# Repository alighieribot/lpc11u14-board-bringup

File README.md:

# Board Bring-Up e Validação de Protótipo Eletrônico Embarcado
## Plataforma de Instrumentação e Controle Baseada no MCU NXP LPC11U14F (ARM Cortex-M0)

)

Este repositório reúne a documentação técnica integral, os projetos de engenharia eletrônica (esquemático elétrico, layout de PCI de 2 camadas e modelos 3D desenvolvidos no KiCad 9) e o firmware embarcado modular em linguagem C (bare-metal) estruturado em **Máquina de Estados Finitos (FSM)** para validação física e *board bring-up* de uma placa com o microcontrolador **NXP LPC11U14F** (núcleo ARM Cortex-M0).

O projeto foi concebido e implementado no âmbito da disciplina **PBLE02 (Projeto Baseado em Laboratório de Engenharia / Projeto de Hardware e Firmware)** do **Instituto de Engenharia de Sistemas e Tecnologia da Informação (IESTI)** da **Universidade Federal de Itajubá (UNIFEI)**, sob a orientação do **Prof. Dr. Rodrigo Maximiano Antunes de Almeida**.

---

## Equipe do Projeto (Grupo 1)

| Integrante | Matrícula |
| :--- | :---: |
| **Leonardo Mendonça Costa** | `2024001025` |
| **Fabricio Augusto Antonio** | `2025000031` |
| **Pedro Henrique Oliveira Francisco** | `2022003245` |
| **Luis Gustavo Ribeiro Chacon** | `2025004890` |

**Agradecimentos Institucionais:**
À equipe técnica de laboratório do IESTI/UNIFEI, em especial aos técnicos em eletrônica **José Anderson Reis** e **Nedson Joaquim Maia**, pelo auxílio instrumental de bancada, suporte de montagem e retrabalho de protótipos; e ao **Prof. Dr. Rodrigo Maximiano Antunes de Almeida** pelas orientações e direcionamento técnico durante a validação experimental.

---

## Visão Geral da Placa de Circuito Impresso (PCB)

A placa física foi projetada respeitando dimensões compactas de $80 \times 80\text{ mm}^2$ em substrato de fibra de vidro FR-4 de duas camadas condutivas, espessura de 1,6 mm, acabamento superficial HASL com chumbo, máscara de solda verde e serigrafia branca, fabricada pela JLCPCB.

| Face Superior 3D (Revisão Final Corrigida) | Face Inferior 3D (Plano de Terra Sólido) |
| :---: | :---: |
|  |  |

| Comparativo Histórico: Face Superior 3D Original |
| :---: |
|  |

> **BOM Interativo (iBOM):** O repositório inclui a lista de materiais interativa gerada pelo plugin *Interactive HTML BOM*. Para navegar visualmente por cada componente, ilha e footprint na placa, abra em seu navegador o arquivo [`KiCad/Projeto_Final/bom/ibom.html`](KiCad/Projeto_Final/bom/ibom.html).

---

## Arquitetura de Hardware & Subcircuitos

O sistema é subdividido em 5 subsistemas funcionais integrados:

```mermaid
graph TD
    PS["1. Subcircuito de Alimentação<br/>Jack DC 7-12V -> LD1117 5.0V & 3.3V"] --> MCU["2. Processamento Central<br/>NXP LPC11U14F ARM Cortex-M0 @ 48MHz"]
    PS --> COMM["5. Comunicação Serial<br/>FTDI FT232RL USB-UART"]
    PS --> HMI["3. Interface Homem-Máquina<br/>LCD 16x2, Encoder Bourns, 4x Teclas, LEDs"]
    PS --> PERIPH["4. Periféricos & Armazenamento<br/>EEPROM I2C 24LC512 + Headers Expansão"]

    MCU <-->|"UART 115200 bps"| COMM
    MCU <-->|"Barramento I2C 3.3V"| PERIPH
    MCU <-->|"GPIOs & PWM / Timers"| HMI
    MCU <-->|"ADC 10-bit / SPI / Expansão"| PERIPH
```

### 1. Subcircuito de Alimentação
- **Entrada:** Conector Jack fêmea P4 (PJ-002A) compatível com fontes externas DC na faixa de **7V a 12V**.
- **Proteção:** Diodo Schottky `1N5819HW-7-F` em série para bloqueio contra inversão de polaridade e transientes.
- **Regulação Linear em Cascata:**
  - `LD1117DT50TR` (DPAK): Converte a tensão de entrada para o barramento de **5.0V DC** (alimentação do display LCD).
  - `LD1117S33TR` (SOT-223): Fornece **3.3V DC** regulados (para microcontrolador, transceptor USB e EEPROM).
- **Filtragem e Desacoplamento:** Associação de capacitores eletrolíticos de $10\ \mu\text{F}$ e cerâmicos multicamada X7R de $220\text{ nF}$ nas entradas e saídas. LED piloto indicador de barramento energizado com resistor limitador de $1\text{ k}\Omega$.

---

### 2. Subcircuito de Processamento
- **MCU:** NXP `LPC11U14F/201` em encapsulamento LQFP-48, núcleo ARM Cortex-M0 operando a até **48 MHz**, dotado de 32 KB de memória Flash, 6 KB de SRAM, 4 KB de EEPROM integrada e controlador USB full-speed.
- **Oscilador de Clock:** Cristal de quartzo de alta precisão de **12.000 MHz** (CTS ATS12A) associado a capacitores de carga externos dimensionados em **18 pF**.
- **Reset e Bootloader ISP:**
  - Reset mestre com botão táctil `SW1`, pull-up de $4.7\text{ k}\Omega$ e capacitor de debounce de $10\ \mu\text{F}$.
  - Chave de programação em sistema (ISP) `SW6` com pull-up, interligada ao pino oficial de bootloader `PIO0_1` (Pino 4).
- **Depuração / Programação:** Header SWD (*Serial Wire Debug*) com pinos `SWDIO` (Pino 39) e `SWDCLK` (Pino 29).

| Processamento Original (LPC1114) | Processamento Corrigido (LPC11U14F) |
| :---: | :---: |
|  |  |

---

### 3. Subcircuito de Interação com o Usuário (IHM)
- **Display Alfanumérico:** LCD 16×2 (compatível com controlador HD44780 / JHD162A) operando em barramento paralelo de **4 bits** (`D4` a `D7`), com controle pelos sinais `RS`, `R/W` e `ENABLE`. Ajuste de contraste via trimpot de precisão de $10\text{ k}\Omega$.
- **Encoder Rotativo Incremental:** Bourns `PEC12R` com 24 pulsos por rotação, canais em quadratura A e B, botão de clique central e filtro RC passivo anti-ruído mecânico (*debounce*).
- **Teclado Táctil:** 4 chaves tácteis push-button (`SW2`, `SW3`, `SW4`, `SW5`) com resistores de pull-up de $10\text{ k}\Omega$.
- **Sinalizadores Visuais:** Três LEDs SMD (`D2`, `D3`, `D4`) acionados diretamente pelas saídas digitais do microcontrolador com resistores limitadores de $100\ \Omega$.

| Interação Original | Interação Corrigida (Ajuste de R e C) |
| :---: | :---: |
|  |  |

---

### 4. Subcircuito de Periféricos & Armazenamento
- **Memória EEPROM Externa:** Microchip `24LC512` (512 Kbit / 64 KByte) operando via barramento **I²C** com resistores de pull-up de $1\text{ k}\Omega$ polarizados em 3.3V.
- **Barramentos de Expansão:** Headers macho de passo 2.54 mm (`J4` a `J8`) expondo portas analógicas do ADC (10 bits), barramento SPI (`SCK`, `MISO`, `MOSI`, `SSEL`), alimentação e GPIOs livres.
- **Condicionamento de Sinal:** Canal de amplificação operacional para transdução de sinais analógicos externos com compensação de ganho em software (`GANHO_AMPOP`).

---

### 5. Subcircuito de Comunicação Serial
- **Transceptor USB-UART:** Chip dedicado FTDI `FT232RL` (SSOP-28) realizando a ponte entre o barramento USB da estação hospedeira e as portas seriais assíncronas do microcontrolador (`PIO0_18/RXD` e `PIO0_19/TXD`).
- **Conector Físico:** Porta Mini-USB Tipo B com filtragem e desacoplamento de alta frequência.

| Comunicação Original | Comunicação Corrigida (Isolamento VBUS) |
| :---: | :---: |
|  |  |

---

### Verificação de Regras Elétricas (ERC) e de Layout (DRC)
Durante o desenvolvimento no KiCad 9, a conformidade de conexões e fabricabilidade foi atestada:

| Esquema Elétrico ERC Original (Avisos) | Esquema Elétrico ERC Corrigido (0 Erros) |
| :---: | :---: |
|  |  |

| DRC da Placa Original (Conflitos e Ilhas Isoladas) | DRC da Placa Corrigida (100% Validada) |
| :---: | :---: |
|  |  |

---

## Board Bring-Up: Modificações Físicas & Memorial de Cálculos

Durante a etapa prática de validação e *bring-up* em bancada com osciloscópio digital e multímetro de precisão, foram diagnosticadas discrepâncias no circuito original que demandaram **engenharia de retrabalho** (cortes de trilhas na PCI, soldagem de *jumpers* de precisão e readequação de componentes passivos).

### 1. Dimensionamento dos Capacitores de Carga do Cristal Oscilador (C25 e C26)
- **Problema Diagnosticado:** O esquemático original previa erroneamente capacitores de $10\ \mu\text{F}$ nas linhas `XTALIN` e `XTALOUT`. O excesso de reatância capacitiva aterrou os sinais de alta frequência e impediu qualquer ressonância do cristal de quartzo de 12 MHz, travando a inicialização do núcleo ARM.
- **Memorial de Cálculo da Capacitância Externa ($C_{ext}$):**
  O cristal de quartzo de 12 MHz (CTS ATS12A) especifica capacitância de carga nominal $C_L = 12\text{ pF}$. A capacitância parasita combinada das trilhas da PCI e pinos do chip é estimada em $C_s \approx 3\text{ pF}$. Como os dois capacitores de carga externos são idênticos ($C_1 = C_2 = C_{ext}$):
  $$C_L = \frac{C_1 \cdot C_2}{C_1 + C_2} + C_s = \frac{C_{ext}^2}{2 \cdot C_{ext}} + C_s = \frac{C_{ext}}{2} + C_s$$
  $$C_{ext} = 2 \cdot (C_L - C_s) = 2 \cdot (12\text{ pF} - 3\text{ pF}) = 2 \cdot 9\text{ pF} = \mathbf{18\text{ pF}}$$
- **Ação Realizada:** Substituição imediata dos capacitores $C_{25}$ e $C_{26}$ por cerâmicos C0G/NP0 de **18 pF**, viabilizando a oscilação estável do clock a 12 MHz.

---

### 2. Constante de Tempo do Filtro RC do Encoder Rotativo
- **Problema Diagnosticado:** O filtro RC do encoder `SW7` continha capacitores de $10\ \mu\text{F}$ com pull-ups de $10\text{ k}\Omega$, gerando constante de tempo $\tau = 100\text{ ms}$. Isso deformava os trens de pulso de quadratura durante giros normais, impossibilitando a leitura do sentido de rotação.
- **Memorial de Cálculo de Resposta em Frequência e Debounce:**
  Para filtrar o repique de contato mecânico (*bouncing*, típico de dezenas a centenas de microssegundos conforme Bourns) sem degradar giros manuais rápidos, os capacitores foram redimensionados para $C = 10\text{ nF}$:
  $$\tau = R \cdot C = (10 \times 10^3\ \Omega) \cdot (10 \times 10^{-9}\text{ F}) = 100\ \mu\text{s} = \mathbf{0.1\text{ ms}}$$
  A frequência de corte do filtro passa-baixas resultante é:
  $$f_c = \frac{1}{2 \cdot \pi \cdot R \cdot C} = \frac{1}{2 \cdot \pi \cdot 100\ \mu\text{s}} \approx \mathbf{1.59\text{ kHz}}$$
- **Ação Realizada:** Troca dos capacitores para **10 nF**, garantindo imunidade a repiques mecânicos e leitura instantânea de rotação em ambos os sentidos.

---

### 3. Tensão Lógica e Corrente de Dreno (Sink) no Barramento I²C
- **Problema Diagnosticado:** Os resistores de pull-up $R_1$ e $R_2$ ($1\text{ k}\Omega$) estavam conectados à malha de **5.0V**. Pela especificação oficial do protocolo I²C, a corrente de dreno em nível baixo ($I_{OL}$) em saídas open-drain não deve ultrapassar $3.0\text{ mA}$ para assegurar $V_{OL} \le 0.4\text{ V}$.
  $$I_{OL(5V)} = \frac{5.0\text{ V} - 0.4\text{ V}}{1\text{ k}\Omega} = \mathbf{4.6\text{ mA}} \quad (\text{Excede o limite normativo de 3 mA!})$$
- **Memorial de Cálculo com Alimentação Corrigida em 3.3V:**
  $$I_{OL(3.3V)} = \frac{3.3\text{ V} - 0.4\text{ V}}{1\text{ k}\Omega} = \mathbf{2.9\text{ mA}} \quad (< 3.0\text{ mA}, \text{em estrita conformidade})$$
- **Ação Realizada:** Corte da ilha de 5V e ligação por *jumper* dos resistores de pull-up $R_1$ e $R_2$ à tensão de 3.3V do pino 8 da EEPROM (U5).

---

### 4. Dimensionamento dos Resistores Limitadores dos LEDs (D2, D3, D4)
- **Problema Diagnosticado:** Com resistores originais de $1\text{ k}\Omega$ sob alimentação de 3.3V e queda direta $V_F = 2.0\text{ V}$ dos LEDs verdes Lite-On, a corrente era inexpressiva:
  $$I_{LED} = \frac{3.3\text{ V} - 2.0\text{ V}}{1\text{ k}\Omega} = \mathbf{1.3\text{ mA}}$$
- **Memorial de Cálculo para Corrente Nominal de Sinalização ($R_d$):**
  Para assegurar fluxo luminoso adequado com corrente de $\approx 13\text{ mA}$ (dentro do limite máximo de 40 mA por porta do LPC11U14F):
  $$R_d = \frac{V_{DD} - V_F}{I_{desejado}} = \frac{3.3\text{ V} - 2.0\text{ V}}{13\text{ mA}} = \frac{1.3\text{ V}}{0.013\text{ A}} = \mathbf{100\ \Omega}$$
- **Ação Realizada:** Instalação de resistores SMD de **100 Ω** (código 101).

---

### 5. Retrabalhos Físicos de Roteamento (Cortes e Jumpers)
1. **Migração LPC1114 -> LPC11U14F:** Adaptação da distribuição de pinos do microcontrolador e inclusão do header `LPC11Uxx.h` no firmware.
2. **LCD ENABLE (E):** Trilha cortada no pino 19 (`USB_DM`) e religada por *jumper* ao pino 13 (`PIO1_20`).
3. **LCD DATA 4 (DB4):** Trilha cortada no pino 20 (`USB_DP`) e religada por *jumper* ao pino 24 (`PIO1_28`).
4. **Tecla Bootloader ISP (SW6):** Desconectada do pino 25 e religada por *jumper* ao pino 4 (`PIO0_1`), pino de hardware que força a entrada no bootloader ISP ROM do LPC11U14F.
5. **Linha de Expansão EXP01:** Desviada para o pino 1 do conector `J5` (associada ao pino 25 `PIO1_31`).
6. **Proteção de Barramento USB (VBUS):** Corte da trilha que injetava 5V do conector Mini-USB no barramento da placa, eliminando circulação de corrente indesejada entre a fonte externa e o computador hospedeiro.

---

## Arquitetura de Software & Firmware Embarcado

O firmware foi desenvolvido em **C (padrão C99)** bare-metal para microcontroladores ARM Cortex-M0, estruturado em uma arquitetura orientada a eventos e baseada em uma **Máquina de Estados Finitos (FSM - Finite State Machine)** determinística.

### Diagrama UML da Arquitetura do Software
O design modular desacopla a camada de aplicação/controle da camada de drivers de baixo nível de hardware:

---

### Diagrama da Máquina de Estados Finitos (FSM)

A lógica central da aplicação é governada por estados mutuamente exclusivos que respondem a eventos gerados assincronamente pelo teclado, encoder, temporizadores ou recepção serial:

#### Tabela de Estados Principais:
| Estado | Descrição Funcional | Transições & Eventos |
| :--- | :--- | :--- |
| `STATE_INIT` | Inicialização dos periféricos (GPIO, I²C, UART, Timer, LCD), restauração dos parâmetros salvos na EEPROM. | Avança automaticamente para `STATE_NAV_MAIN`. |
| `STATE_NAV_MAIN` | Carrossel principal de menus: Horas, Alarme, Leitura do Sensor e Idioma. | `EV_UP` (SW5) / `EV_DOWN` (SW3) alternam os menus. `EV_ENTER` (SW4) acessa o modo de edição. |
| `STATE_HORAS` | Exibição em tempo real do relógio RTC no display LCD. | `EV_ENTER` desvia para `STATE_MUDAR_HORAS`. |
| `STATE_MUDAR_HORAS`| Edição de horas e minutos em memória RAM. | Rotação horária (`EV_ENC_ROT_CW`) ou anti-horária (`EV_ENC_ROT_CCW`) ajusta o valor. Clique do encoder (`EV_CANCEL`) cancela. `EV_ENTER` salva na EEPROM (`STATE_MEM_SAVE`). |
| `STATE_ALARME` | Monitoramento dos limites de disparo de alarme de janela (Low e High). | `EV_ENTER` acessa edição dos limites `STATE_ALARME_L` e `STATE_ALARME_H`. |
| `STATE_SENSOR` | Aquisição contínua do valor analógico pelo conversor A/D (10 bits) com conversão em tensão ($V$). | Se a leitura violar os limites configurados, dispara `EV_OUT_OF_RANGE`. |
| `STATE_OUT_OF_RANGE`| **Estado de Segurança:** Alerta visual com piscamento em alta prioridade de LEDs e mensagem no LCD indicando condição anômala. | O sistema trava o alerta até que a variável analógica retorne à faixa de tolerância. |
| `STATE_IDIOMA` | Exibição do idioma de interface ativo (Português / Inglês). | `EV_ENTER` desvia para `STATE_MUDAR_IDIOMA`. |
| `STATE_MEM_SAVE` | Executa a rotina de gravação não-volátil na EEPROM externa via barramento I²C. | Retorna para `STATE_NAV_MAIN` após sucesso. |
| `STATE_UI_IDLE` | Modo de economia de energia por inatividade de teclas e escurecimento de display (*backlight*). | Disparado por `EV_TIMEOUT`. Qualquer tecla (`EV_ANY_KEY`) acorda o sistema. |
| `STATE_FAULT` | Tratamento de falha crítica (erro de barramento I²C ou perda de integridade). | Recuperação via `SW1` (Reset de hardware). |

---

### Estrutura Modular do Código-Fonte (`Código/PBLE02/src/`)
- **`programa.c / .h`**: Ponto de entrada (`main`), rotinas de inicialização de clock e laço infinito (`smLoop` e `processaComandoSerial`).
- **`ctl/stateMachine.c / .h`**: Implementação da FSM, definição dos estados e lógica de transição.
- **`ctl/event.c / .h`**: Amostragem periódica de periféricos e fila circular de eventos (`EV_UP`, `EV_DOWN`, `EV_ENTER`, `EV_CANCEL`, etc.).
- **`ctl/timer.c / .h`**: Configuração da interrupção periódica SysTick (base de tempo de 1 ms).
- **`ctl/var.c / .h`**: Gestão de variáveis globais do sistema, strings de menu multilíngue e controle de alarmes.
- **`ctl/output.c / .h`**: Mapeamento das saídas visuais e atualização de display.
- **`hardware/LCD.c / .h`**: Driver de baixo nível para display alfanumérico HD44780 em barramento de 4 bits.
- **`hardware/ENCODER.c / .h`**: Decodificador de quadratura dos canais A/B do encoder Bourns.
- **`hardware/Teclado.c / .h`**: Varredura das teclas tácteis de navegação com debounce digital.
- **`hardware/EEPROM.c / .h` & `I2C.c / .h`**: Driver mestre I²C para leitura/gravação não-volátil de blocos na memória 24LC512.
- **`hardware/RTC.c / .h`**: Relógio de tempo real implementado por software com base no SysTick.
- **`hardware/Serial.c / .h`**: Driver assíncrono UART com buffer circular de recepção/transmissão e decodificador ASCII.
- **`hardware/ADC.c / .h` & `DAC.c / .h`**: Amostragem analógica de 10 bits e conversão D/A.
- **`hardware/LED.c / .h`**: Acionamento e controle de estados dos LEDs.

---

### Protocolo de Telemetria e Comandos Serial (UART @ 115200 bps)

O transceptor USB-Serial executa um *parser* de comandos ASCII permitindo tanto a consulta (*getters*) quanto a calibração remota de parâmetros (*setters*):

| Comando Serial | Direção | Formato da Resposta / Ação | Exemplo de Saída |
| :--- | :---: | :--- | :--- |
| `gettime` | Entrada | Retorna o horário atual do RTC interno | `#time=14:32:05#` |
| `getsensor` | Entrada | Retorna o valor raw do ADC (10 bits) e a tensão calibrada em Volts | `#sensor=0512/1.65V#` |
| `getalarmelow` | Entrada | Retorna o limiar inferior do alarme | `#alarmeLow=250#` |
| `getalarmehigh`| Entrada | Retorna o limiar superior do alarme | `#alarmeHigh=400#` |
| `alarmelow:<val>` | Entrada | Ajusta o limiar inferior e grava na EEPROM | `#alarmeLow=280#` |
| `alarmehigh:<val>`| Entrada | Ajusta o limiar superior e grava na EEPROM | `#alarmeHigh=420#` |
| `time:<hh>:<mm>:<ss>`| Entrada| Sincroniza o relógio RTC de software | `#time=09:15:00#` |
| `language:<0\|1>`| Entrada | Seleciona o idioma (0: Português, 1: Inglês) | `#language=0#` |
| `'0'`, `'1'`, `'2'`, `'3'` | Entrada | Comuta (*toggle*) o estado lógico dos LEDs indicadores de status | Ecoa o caractere transmitido |

---

## Mapa de Pinos do Microcontrolador LPC11U14F

Diagrama oficial do encapsulamento LQFP-48 e mapa de conexão das portas com o hardware físico:

<details open>
<summary><b>Tabela Completa dos 48 Pinos do LPC11U14F</b></summary>

| Pino | Porta GPIO | Função / Conexão no Esquemático | Destino Físico |
| :---: | :---: | :--- | :--- |
| 1 | `PIO1_25` | `EXP10` | Header de Expansão J7.3 |
| 2 | `PIO1_19` | `SS` (SPI Slave Select) | Header de Expansão J6.5 |
| 3 | `PIO0_0` | `RESET` | Botão Reset SW1 com pull-up |
| 4 | `PIO0_1` | `ISP` (Bootloader de Gravação) | Botão táctil SW6 (Jumper de correção) |
| 5 | `VSS` | Terra Digital (`GND`) | Plano de Terra |
| 6 | `XTALIN` | Entrada do Oscilador de Quartzo | Cristal 12MHz Pino 1 / C25 (18pF) |
| 7 | `XTALOUT`| Saída do Oscilador de Quartzo | Cristal 12MHz Pino 3 / C26 (18pF) |
| 8 | `VDD` | Alimentação Positiva `+3.3V` | Barramento de 3.3V |
| 9 | `PIO0_20` | `EXP04` | Header de Expansão J5.4 |
| 10 | `PIO0_2` | Canal A do Encoder Rotativo (`SWA`) | Chave Bourns SW7.A1 |
| 11 | `PIO1_26` | Canal B do Encoder Rotativo (`SWB`) | Chave Bourns SW7.B1 |
| 12 | `PIO1_27` | Botão Integrado do Encoder (`S1`) | Chave Bourns SW7.1 |
| 13 | `PIO1_20` | Habilitação do LCD (`ENABLE` / `E`) | Conector LCD J9.6 (Jumper de correção) |
| 14 | `PIO0_3` | Proteção de Escrita da EEPROM (`WP`) | Pino 7 da EEPROM U5 |
| 15 | `PIO0_4` | Clock I²C (`SCL`) | Pino 6 da EEPROM U5 (Pull-up em 3.3V) |
| 16 | `PIO0_5` | Dados I²C (`SDA`) | Pino 5 da EEPROM U5 (Pull-up em 3.3V) |
| 17 | `PIO0_21` | Seleção de Registrador LCD (`RS`) | Conector LCD J9.4 |
| 18 | `PIO1_23` | Leitura/Escrita do LCD (`R/W`) | Conector LCD J9.5 |
| 19 | `USB_DM` | `EXP07` (Livre após corte do LCD) | Header de Expansão J5.7 |
| 20 | `USB_DP` | `EXP11` (Livre após corte do LCD) | Header de Expansão J7.4 |
| 21 | `PIO1_24` | Barramento de Dados LCD (`D5`) | Conector LCD J9.12 |
| 22 | `PIO0_6` | Barramento de Dados LCD (`D6`) | Conector LCD J9.13 |
| 23 | `PIO0_7` | Barramento de Dados LCD (`D7`) | Conector LCD J9.14 |
| 24 | `PIO1_28` | Barramento de Dados LCD (`D4`) | Conector LCD J9.11 (Jumper de correção) |
| 25 | `PIO1_31` | `EXP01` | Header de Expansão J5.1 |
| 26 | `PIO1_21` | `EXP08` | Header de Expansão J7.1 |
| 27 | `PIO0_8` | Linha SPI `MISO` | Header de Expansão J6.4 |
| 28 | `PIO0_9` | Linha SPI `MOSI` | Header de Expansão J6.3 |
| 29 | `PIO0_10` | Depuração SWD Clock (`SWDCLK`) | Header de Gravação J3.4 |
| 30 | `PIO0_22` | `EXP05` | Header de Expansão J5.5 |
| 31 | `PIO1_29` | Linha SPI Clock (`SCK`) | Header de Expansão J6.6 |
| 32 | `PIO0_11` | LED Indicador de Status 1 | LED D3.2 |
| 33 | `PIO0_12` | LED Indicador de Status 2 | LED D4.2 |
| 34 | `PIO0_13` | Tecla Navegação Baixo (`SW3`) | Chave Táctil SW5.3 |
| 35 | `PIO0_14` | Tecla Confirmação Enter (`SW2`) | Chave Táctil SW4.3 |
| 36 | `PIO1_13` | Tecla Navegação Cima (`SW1`) | Chave Táctil SW3.3 |
| 37 | `PIO1_14` | `EXP12` | Header de Expansão J7.5 |
| 38 | `PIO1_22` | `EXP09` | Header de Expansão J7.2 |
| 39 | `PIO0_15` | Depuração SWD Dados (`SWDIO`) | Header de Gravação J3.2 |
| 40 | `PIO0_16` | `EXP02` | Header de Expansão J5.2 |
| 41 | `VSS` | Terra Digital (`GND`) | Plano de Terra |
| 42 | `PIO0_23` | `EXP06` | Header de Expansão J5.6 |
| 43 | `PIO1_15` | `EXP13` | Header de Expansão J7.6 |
| 44 | `VDD` | Alimentação Positiva `+3.3V` | Barramento de 3.3V |
| 45 | `PIO0_17` | Linha Analógica ADC (`EXP03`) | Header de Expansão J5.3 |
| 46 | `PIO0_18` | Recepção Serial UART (`RXD`) | Saída TXD do transceptor FT232RL |
| 47 | `PIO0_19` | Transmissão Serial UART (`TXD`) | Entrada RXD do transceptor FT232RL |
| 48 | `PIO1_16` | `EXP14` | Header de Expansão J7.7 |

</details>

---

## Balanço Elétrico & Consumo de Potência

A estimativa do consumo total do protótipo foi calculada considerando correntes máximas em regime contínuo:

| Subsistema / Componente | Tensão ($V$) | Corrente Máx. Estimada ($mA$) | Potência Ativa ($W$) |
| :--- | :---: | :---: | :---: |
| Microcontrolador NXP LPC11U14F | $3.3\text{ V}$ | $100\text{ mA}$ | $0.330\text{ W}$ |
| Transceptor USB-Serial FT232RL | $3.3\text{ V}$ | $25\text{ mA}$ | $0.082\text{ W}$ |
| Memória EEPROM 24LC512 | $3.3\text{ V}$ | $3\text{ mA}$ | $0.010\text{ W}$ |
| Módulo Display LCD 16×2 (com Backlight)| $5.0\text{ V}$ | $120\text{ mA}$ | $0.600\text{ W}$ |
| LEDs Indicadores (3x) | $3.3\text{ V}$ | $39\text{ mA}$ | $0.129\text{ W}$ |
| Carga de Expansão / Sensores (Reserva Máx.) | $3.3\text{ V} / 5.0\text{ V}$ | $\approx 600\text{ mA}$ | $\approx 3.080\text{ W}$ |
| **Total Máximo Projetado em Carga Plena** | ‒ | ‒ | **$\approx 4.23\text{ W}$** |

---

## Orçamento e Custos de Fabricação

- **Lote de Componentes Eletrônicos (BOM):** **US$ 29,54** (aquisição em distribuidores autorizados como Mouser e Digi-Key).
- **Manufatura das Placas (JLCPCB):** **US$ 2,00** (lote com 5 unidades em FR-4 dupla face, 1.6 mm, 1 oz cobre, acabamento HASL).
- **Logística e Envio Internacional:** **US$ 3,30** (frete econômico internacional).
- **Investimento Consolidado:** **US$ 34,84** (custo unitário de fabricação da placa avulsa de apenas US$ 1,06).

---

## Guia de Compilação e Gravação

### 1. Ferramentas Necessárias
- **KiCad EDA:** Versão 9.0.2 ou superior.
- **IDE C/C++:** MCUXpresso IDE ou Eclipse com GCC ARM Embedded (`arm-none-eabi-gcc`).
- **Gravador Serial:** **Flash Magic** (ferramenta oficial NXP para microcontroladores LPC).

### 2. Procedimento de Gravação via Bootloader ISP
1. Conecte a placa ao computador utilizando um cabo Mini-USB conectado à porta serial FTDI.
2. Segure pressionado o botão **`SW6` (ISP)**.
3. Pressione e solte o botão **`SW1` (RESET)**.
4. Solte o botão `SW6`. O microcontrolador entrará no bootloader ISP gravado em ROM.
5. Abra o **Flash Magic**, configure:
   - **Device:** `LPC11U14/201`
   - **COM Port:** Porta serial atribuída ao chip FTDI
   - **Baud Rate:** `115200`
   - **Interface:** None (ISP)
   - **Oscillator (MHz):** `12`
6. No campo *Hex File*, selecione o binário compilado localizado em `Código/PBLE02/Release/PBLE02.bin`.
7. Marque *Erase blocks used by Firmware* e clique em **Start** para regravar o microcontrolador.

---

## Estrutura de Diretórios do Repositório

```text
.
├── Código/
│   └── PBLE02/
│       ├── .cproject
│       ├── .project
│       ├── PBLE02.fmx
│       ├── configFlashMagic.fmx
│       └── src/
│           ├── ctl/               # Lógica de Controle, FSM, Temporizador, Eventos
│           │   ├── event.c / .h
│           │   ├── output.c / .h
│           │   ├── stateMachine.c / .h
│           │   ├── timer.c / .h
│           │   └── var.c / .h
│           ├── hardware/          # Drivers dos Periféricos de Baixo Nível
│           │   ├── ADC.c / .h
│           │   ├── DAC.c / .h
│           │   ├── EEPROM.c / .h
│           │   ├── ENCODER.c / .h
│           │   ├── LCD.c / .h
│           │   ├── LED.c / .h
│           │   ├── Memoria.c
│           │   ├── RTC.c / .h
│           │   ├── Serial.c / .h
│           │   └── Teclado.c / .h
│           ├── cr_startup_lpc11xx.c
│           ├── I2C.c / .h
│           ├── programa.c / .h    # Ponto de entrada (main) e laço operacional
│           ├── sysinit.c
│           └── util.c / .h
├── KiCad/
│   └── Projeto_Final/
│       ├── bom/
│       │   └── ibom.html          # Interactive HTML BOM (iBOM dinâmico)
│       ├── Footprints/            # Bibliotecas de footprints locais
│       ├── Projeto_Final.kicad_pcb # Layout da placa de circuito impresso
│       ├── Projeto_Final.kicad_sch # Esquema elétrico hierárquico
│       ├── Projeto_Final.kicad_pro # Arquivo de projeto do KiCad
│       └── sym-lib-table
├── docs/
│   └── images/                    # Imagens, renderizações 3D, diagramas e fotos
│       ├── pcb_3d_top_corrected.png
│       ├── pcb_3d_bottom_corrected.png
│       ├── pcb_3d_top_original.png
│       ├── fig01_circuito_alimentacao.png
│       ├── fig02_circuito_processamento_original.png
│       ├── fig03_circuito_processamento_corrigido.png
│       ├── fig04_circuito_interacao_original.png
│       ├── fig05_circuito_interacao_corrigido.png
│       ├── fig06_circuito_perifericos_original.png
│       ├── fig08_circuito_comunicacao_original.png
│       ├── fig09_circuito_comunicacao_corrigido.png
│       ├── fig10_erc_erros_originais.png
│       ├── fig11_erc_verificacao_corrigida.png
│       ├── drc_errors_original.png
│       ├── drc_report_corrected.png
│       ├── mcu_pinout_lpc11u14.png
│       ├── firmware_fsm_state_machine.png
│       └── uml_software_architecture.svg
├── Documentacao.pdf               # Relatório técnico completo da disciplina (66 páginas)
├── uml.svg                        # Diagrama UML original em vetor
├── .gitignore                     # Filtro de arquivos temporários e binários de build
├── LICENSE                        # Licença MIT
└── README.md                      # Documentação técnica consolidada do repositório
```

---

## Licença

Este projeto é disponibilizado sob os termos da licença **MIT**. Para maiores informações, consulte o arquivo [LICENSE](LICENSE).

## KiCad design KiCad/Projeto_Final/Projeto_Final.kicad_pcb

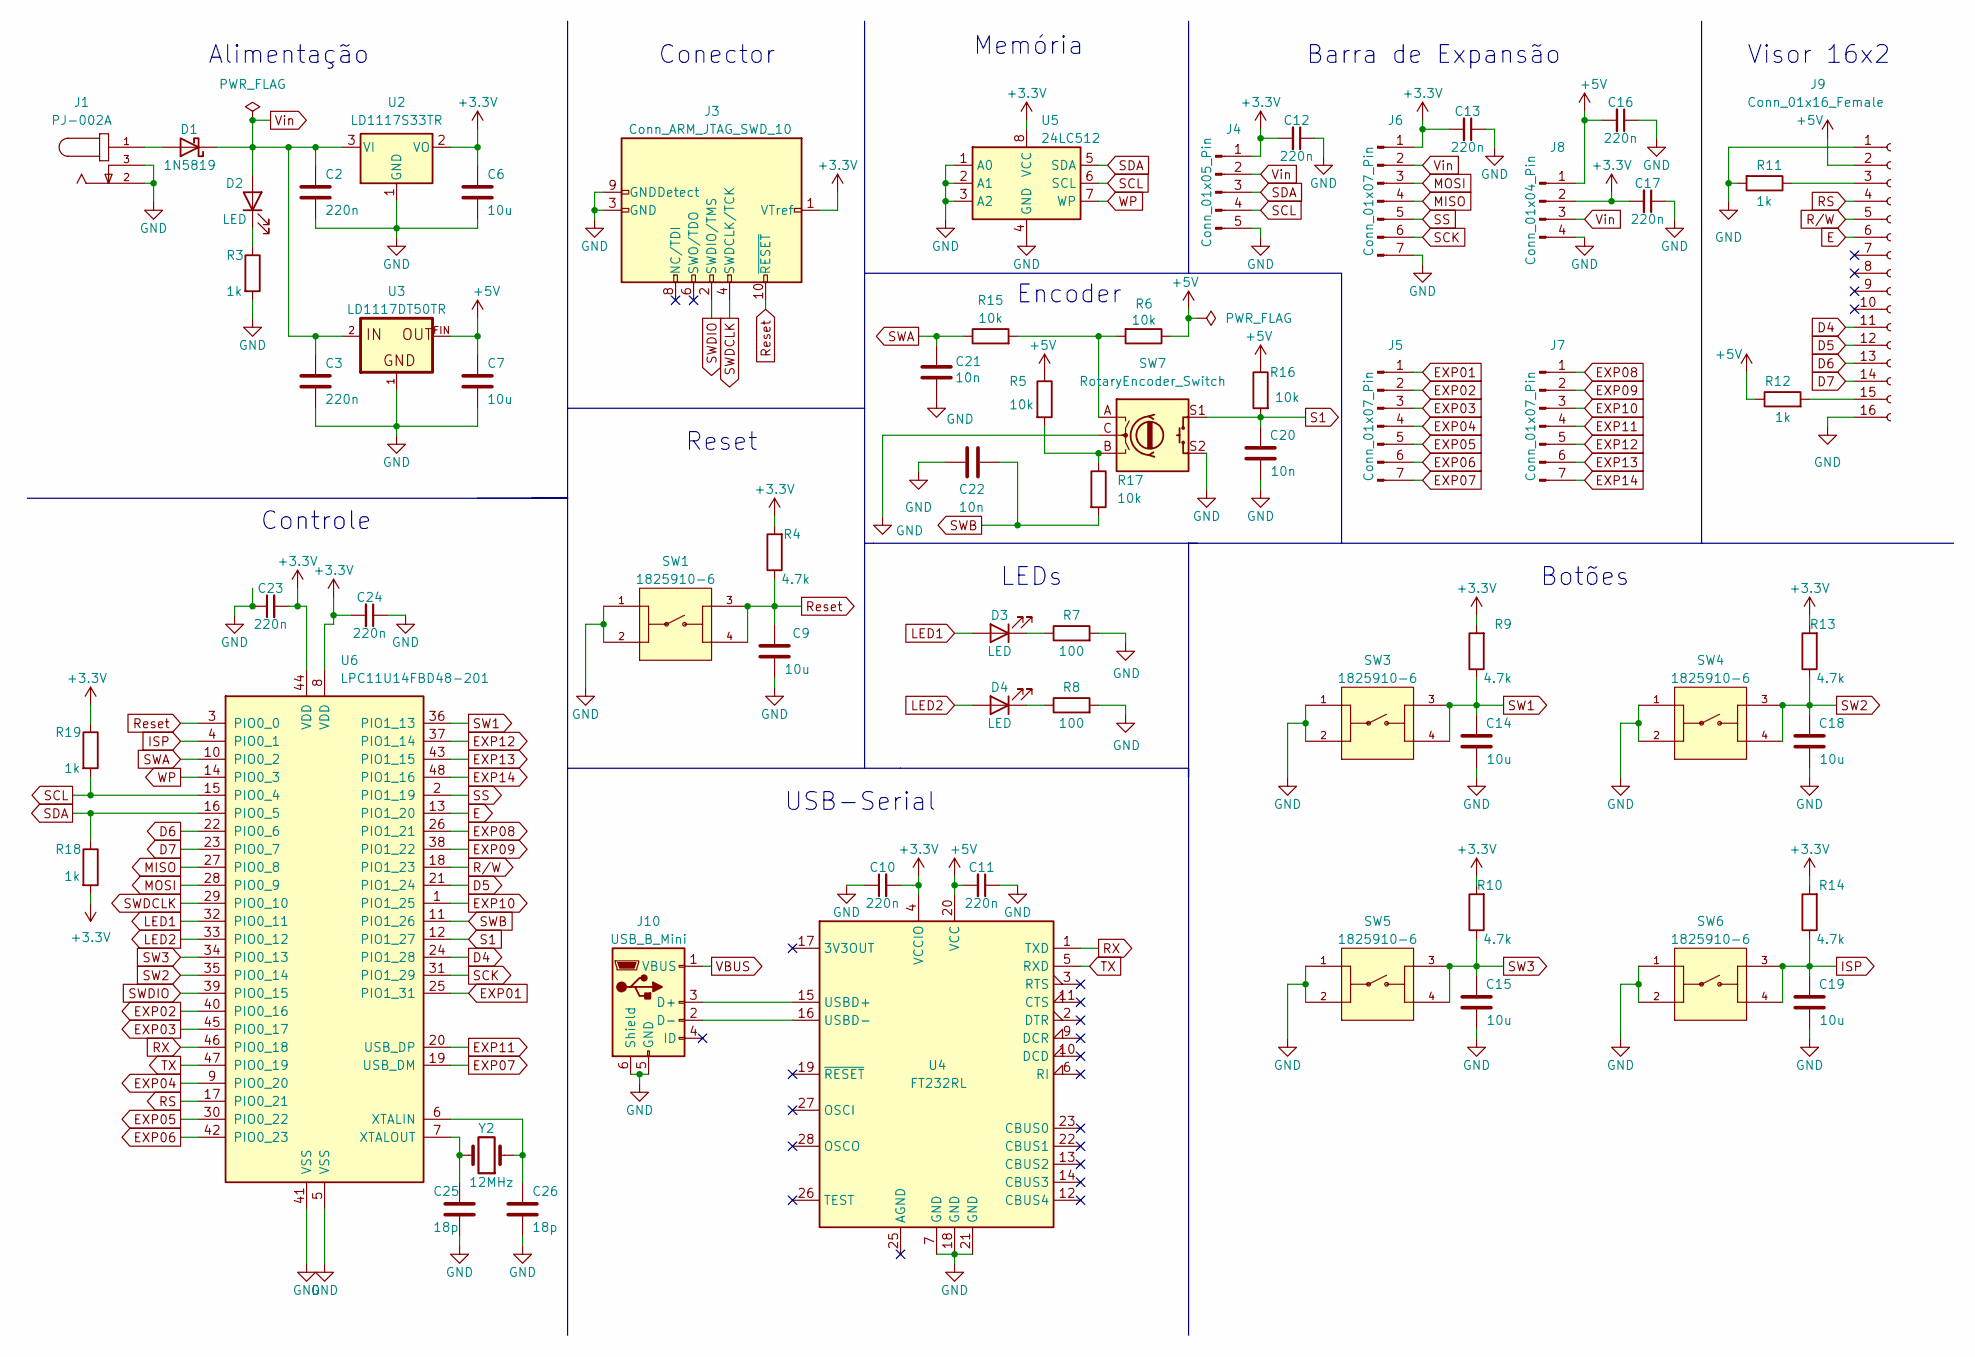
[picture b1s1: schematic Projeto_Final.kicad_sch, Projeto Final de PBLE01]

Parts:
C2, C3, C10, C11, C12, C13, C16, C17, C23, C24: 220n; C_0805_2012Metric
C6, C7, C9, C14, C15, C18, C19: 10u; C_0805_2012Metric
C20, C21, C22: 10n; C_0805_2012Metric
C25, C26: 18p; C_0805_2012Metric
D1: 1N5819; SOD3716X135N
D2, D3, D4: LED; LEDC3216X120N
J1: PJ-002A; CUI_PJ-002A
J3: Conn_ARM_JTAG_SWD_10; SHDR10W99P254_2X5_2032X889X947P
J4: Conn_01x05_Pin; PinHeader_1x05_P2.54mm_Vertical
J5, J6, J7: Conn_01x07_Pin; PinHeader_1x07_P2.54mm_Vertical
J8: Conn_01x04_Pin; PinHeader_1x04_P2.54mm_Vertical
J9: Conn_01x16_Female; PinHeader_1x16_P2.54mm_Vertical
J10: USB_B_Mini; 17340352
R3, R11, R12, R18, R19: 1k; R_0805_2012Metric
R4, R9, R10, R13, R14: 4.7k; R_0805_2012Metric
R5, R6, R15, R16, R17: 10k; R_0805_2012Metric
R7, R8: 100; R_0805_2012Metric
SW1, SW3, SW4, SW5, SW6: 1825910-6; SW_1825910-6-4
SW7: RotaryEncoder_Switch; PEC12R3222FS0024
U2: LD1117S33TR; SOT230P700X180-4N
U3: LD1117DT50TR; DPAK
U4: FT232RL; SOP65P778X200-28N
U5: 24LC512; SOIC127P600X175-8N
U6: LPC11U14FBD48-201; LQFP-48_7x7mm_P0.5mm
Y2: 12MHz; ATS12A

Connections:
+3.3V: C6.1, C10.2, C12.2, C13.2, C17.2, C23.2, C24.2, J3.1 (VTref), J4.1, J6.1, J8.2, R4.2, R9.2, R10.2, R13.2, R14.2, R18.2, R19.1, U2.2 (VO), U4.4 (VCCIO), U5.8 (VCC), U6.8 (VDD), U6.44 (VDD)
+5V: C7.1, C11.2, C16.2, J8.1, J9.2, R5.1, R6.1, R12.1, R16.1, U3.FIN, U4.20 (VCC)
D4: J9.11, U6.24 (PIO1_28)
D5: J9.12, U6.21 (PIO1_24)
D6: J9.13, U6.22 (PIO0_6)
D7: J9.14, U6.23 (PIO0_7)
E: J9.6, U6.13 (PIO1_20)
EXP01: J5.1, U6.25 (PIO1_31)
EXP02: J5.2, U6.40 (PIO0_16)
EXP03: J5.3, U6.45 (PIO0_17)
EXP04: J5.4, U6.9 (PIO0_20)
EXP05: J5.5, U6.30 (PIO0_22)
EXP06: J5.6, U6.42 (PIO0_23)
EXP07: J5.7, U6.19 (USB_DM)
EXP08: J7.1, U6.26 (PIO1_21)
EXP09: J7.2, U6.38 (PIO1_22)
EXP10: J7.3, U6.1 (PIO1_25)
EXP11: J7.4, U6.20 (USB_DP)
EXP12: J7.5, U6.37 (PIO1_14)
EXP13: J7.6, U6.43 (PIO1_15)
EXP14: J7.7, U6.48 (PIO1_16)
GND: C2.2, C3.2, C6.2, C7.2, C9.1, C10.1, C11.1, C12.1, C13.1, C14.1, C15.1, C16.1, C17.1, C18.1, C19.1, C20.1, C21.2, C22.2, C23.1, C24.1, C25.2, C26.2, J1.2, J1.3, J3.3 (GND), J3.5 (GND), J3.9 (GNDDetect), J4.5, J6.7, J8.4, J9.1, J9.16, J10.5 (GND), J10.6 (Shield), R3.2, R7.2, R8.2, R11.2, SW1.1, SW1.2, SW3.1, SW3.2, SW4.1, SW4.2, SW5.1, SW5.2, SW6.1, SW6.2, SW7.C, SW7.S2, U2.1 (GND), U3.1, U4.7 (GND), U4.18 (GND), U4.21 (GND), U5.1 (A0), U5.2 (A1), U5.3 (A2), U5.4 (GND), U6.5 (VSS), U6.41 (VSS)
ISP: C19.2, R14.1, SW6.3, SW6.4, U6.4 (PIO0_1)
LED1: D3.2 (A), U6.32 (PIO0_11)
LED2: D4.2 (A), U6.33 (PIO0_12)
MISO: J6.4, U6.27 (PIO0_8)
MOSI: J6.3, U6.28 (PIO0_9)
unnamed: D1.2 (A), J1.1
unnamed: D2.1 (K), R3.1
unnamed: D3.1 (K), R7.1
unnamed: D4.1 (K), R8.1
unnamed: J9.3, R11.1
unnamed: J9.15, R12.2
unnamed: J10.3 (D+), U4.15 (USBD+)
unnamed: J10.2 (D-), U4.16 (USBD-)
unnamed: R6.2, R15.2, SW7.A
unnamed: R5.2, R17.1, SW7.B
unnamed: C26.1, U6.6 (XTALIN), Y2.1
unnamed: C25.1, U6.7 (XTALOUT), Y2.2
RS: J9.4, U6.17 (PIO0_21)
RX: U4.1 (TXD), U6.46 (PIO0_18)
Reset: C9.2, J3.10 (~RESET), R4.1, SW1.3, SW1.4, U6.3 (PIO0_0)
R/W: J9.5, U6.18 (PIO1_23)
S1: C20.2, R16.2, SW7.S1, U6.12 (PIO1_27)
SCK: J6.6, U6.31 (PIO1_29)
SCL: J4.4, R19.2, U5.6 (SCL), U6.15 (PIO0_4)
SDA: J4.3, R18.1, U5.5 (SDA), U6.16 (PIO0_5)
SS: J6.5, U6.2 (PIO1_19)
SW1: C14.2, R9.1, SW3.3, SW3.4, U6.36 (PIO1_13)
SW2: C18.2, R13.1, SW4.3, SW4.4, U6.35 (PIO0_14)
SW3: C15.2, R10.1, SW5.3, SW5.4, U6.34 (PIO0_13)
SWA: C21.1, R15.1, U6.10 (PIO0_2)
SWB: C22.1, R17.2, U6.11 (PIO1_26)
SWDCLK: J3.4 (SWDCLK/TCK), U6.29 (PIO0_10)
SWDIO: J3.2 (SWDIO/TMS), U6.39 (PIO0_15)
TX: U4.5 (RXD), U6.47 (PIO0_19)
VBUS: J10.1 (VBUS)
Vin: C2.1, C3.1, D1.1 (K), D2.2 (A), J4.2, J6.2, J8.3, U2.3 (VI), U3.2
WP: U5.7 (WP), U6.14 (PIO0_3)

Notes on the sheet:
Alimentação
Controle
LEDs
Visor 16x2
Reset
Memória
USB-Serial
Barra de Expansão
Botões
Encoder
Conector

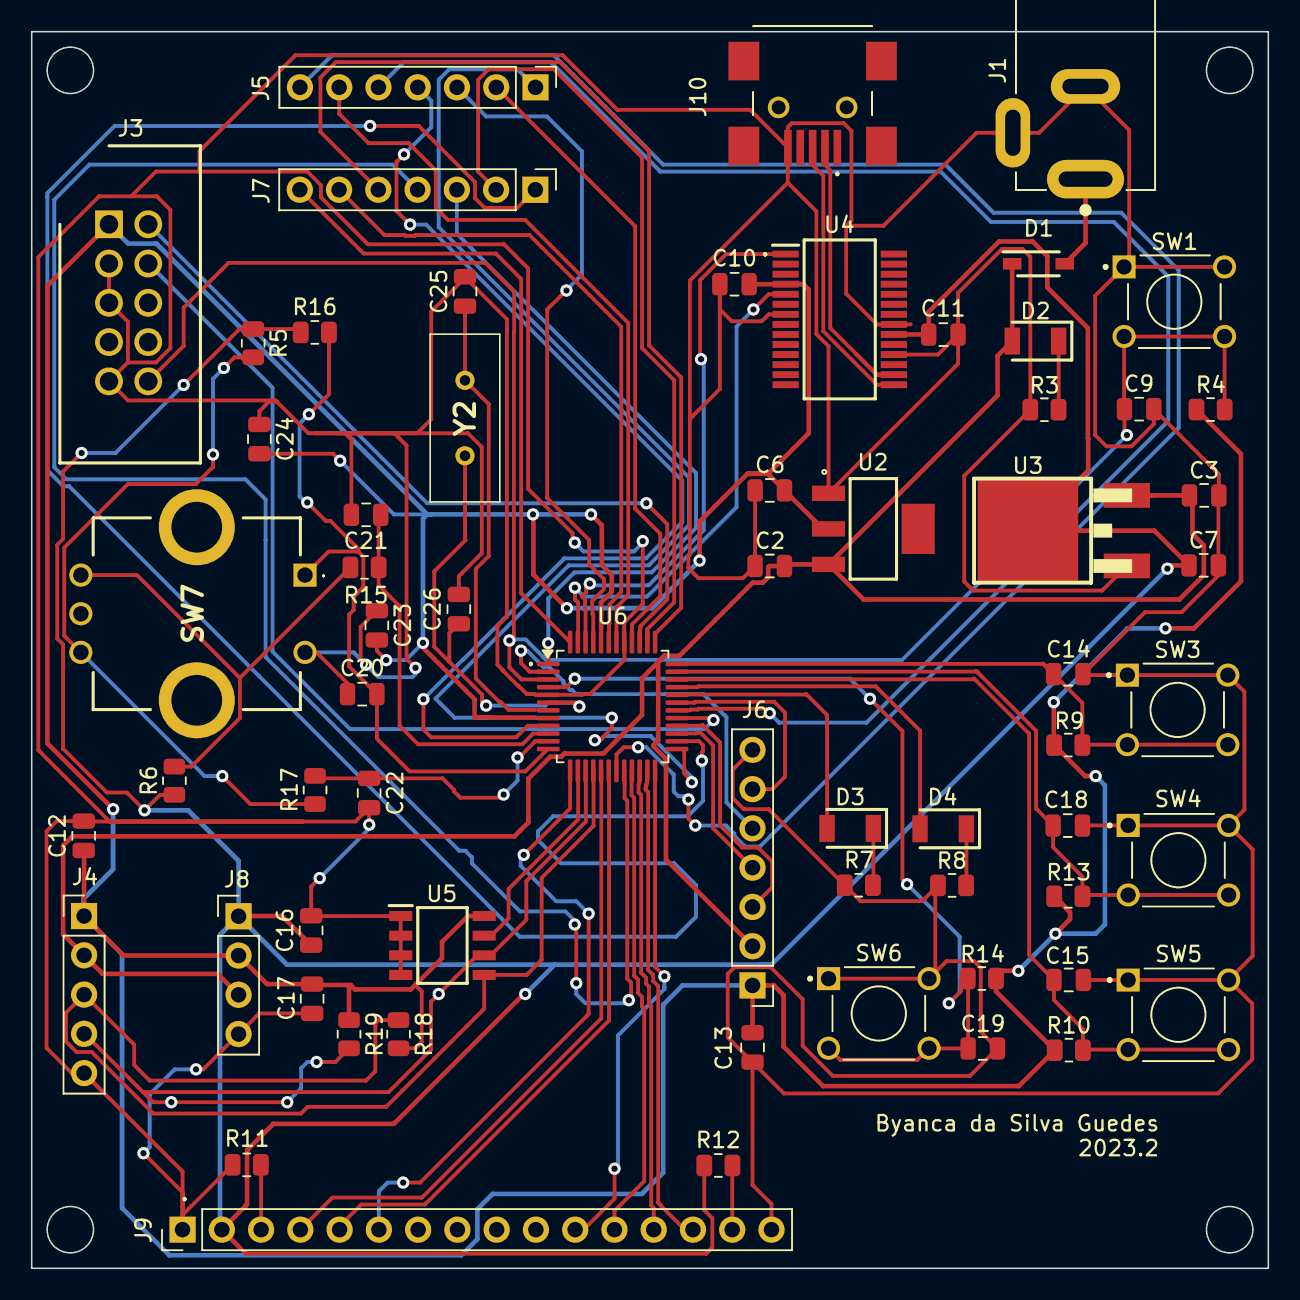
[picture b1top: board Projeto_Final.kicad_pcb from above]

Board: 2 copper layers, 80.0 x 80.0 mm, 64 parts (0 on the bottom side), 58 nets.

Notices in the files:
README.md:
License: MIT
